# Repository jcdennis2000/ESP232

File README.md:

# ESP232

ESP8266 and ESP32 microcontrollers are great! They have built in WiFi, and Bluetooth for the ESP32, in a tiny package! However to program them they need to be put into a bootloader mode, but most programmers can’t do this for you. But now we have the ESPFlash standard!

The ESP232 uses the FTDI232 programmer, with the 1×6 0.1 inch ESPFlash convention. There is a 600mA power regulator on board, which can power the target device, and a USB B connector to connect to your computer.

For more information on the ESPFlash convention see the https://www.superhouse.tv/espflash/.

# Features:
* ESPFlash header in 1×6 0.1inch format.
* 600mA 3.3V voltage regulator.
* Power, TX and RX LEDs.
* FTDI232 USB to Serial converter.

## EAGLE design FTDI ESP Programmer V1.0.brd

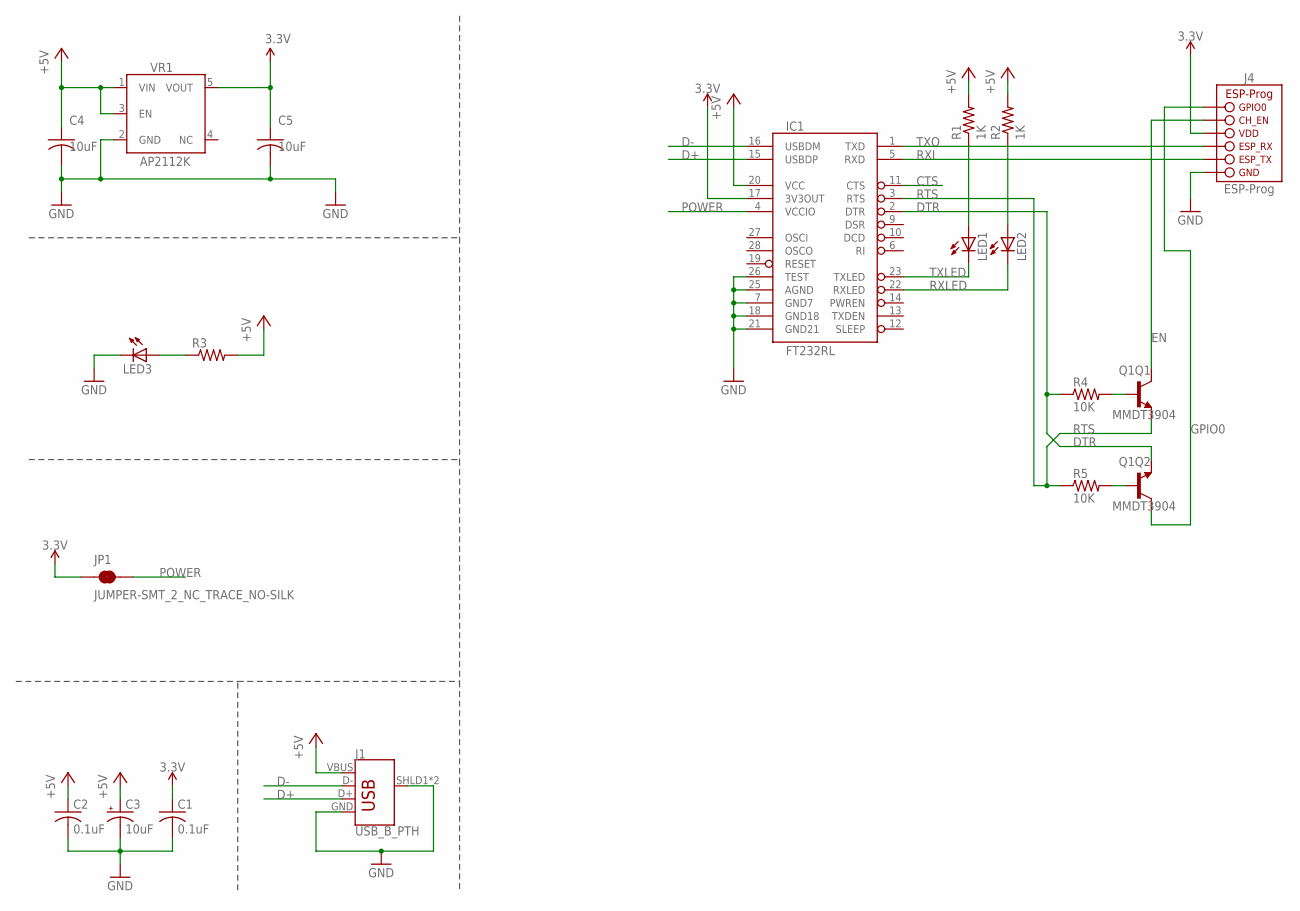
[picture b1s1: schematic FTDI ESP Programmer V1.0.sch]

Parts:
C1, C2: 0.1uF; C0603
C3: 10uF; EIA3216
C4, C5: 10uF; C0603
IC1: FT232RL; SSOP28DB
J1: USB_B_PTH; USB-B-PTH
J4: ESP-PROG-1X6-2.54-SOCKET-RA; 1X6-2.54-SOCKET-RA
JP1: JUMPER-SMT_2_NC_TRACE_NO-SILK; SMT-JUMPER_2_NC_TRACE_NO-SILK
LED1, LED2, LED3: LEDCHIP-LED0805; CHIP-LED0805
Q1: MMDT3904; SOT-363
R1, R2: 1K; R0603
R3: R-USR0603; R0603@1
R4, R5: 10K; R0603@1
VR1: AP2112KSOT25; SOT23-5

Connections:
3.3V: C1.1, C5.1, IC1.17 (3V3OUT), J4.4 (VDD), JP1.1, VR1.5 (VOUT)
+5V: C2.1, C3.+, C4.1, IC1.20 (VCC), J1.VBUS, R1.2, R2.2, R3.2, VR1.1 (VIN), VR1.3 (EN)
CTS: IC1.11 (CTS)
D+: IC1.15 (USBDP), J1.D+
D-: IC1.16 (USBDM), J1.D-
DTR: IC1.2 (DTR), Q1.1 (E), R4.1
EN: J4.5 (CH_EN), Q1.3 (C)
GND: C1.2, C2.2, C3.-, C4.2, C5.2, IC1.7 (GND7), IC1.18 (GND18), IC1.21 (GND21), IC1.25 (AGND), IC1.26 (TEST), J1.GND, J1.SHLD1 (SHIELD), J1.SHLD2 (SHIELD), J4.1 (GND), LED3.C, VR1.2 (GND)
GPIO0: J4.6 (GPIO0), Q1.6 (C)
unnamed: LED1.A, R1.1
unnamed: LED3.A, R3.1
unnamed: LED2.A, R2.1
unnamed: Q1.5 (B), R4.2
unnamed: Q1.2 (B), R5.2
POWER: IC1.4 (VCCIO), JP1.2
RTS: IC1.3 (RTS), Q1.4 (E), R5.1
RXI: IC1.5 (RXD), J4.2 (ESP_TX)
RXLED: IC1.22 (RXLED), LED2.C
TXLED: IC1.23 (TXLED), LED1.C
TXO: IC1.1 (TXD), J4.3 (ESP_RX)

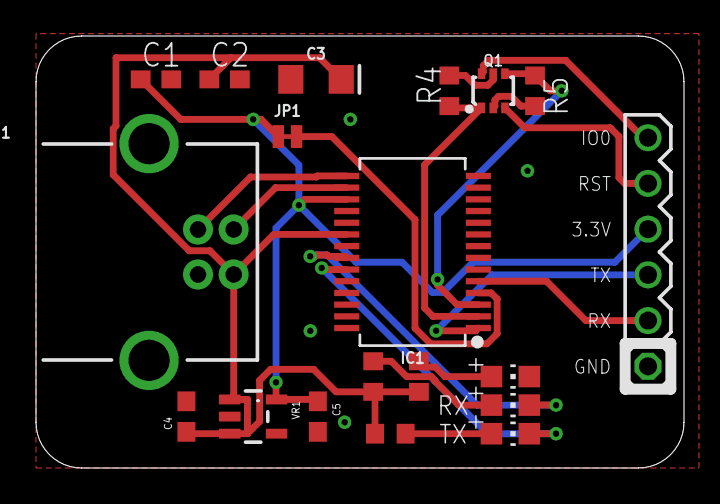
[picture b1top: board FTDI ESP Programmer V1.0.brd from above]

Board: 2 copper layers, 36.0 x 24.0 mm, 19 parts (0 on the bottom side), 19 nets.

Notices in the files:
FTDI ESP Programmer V1.0.brd:
Dennistries Ltd (c) 2020
parts and their libraries:
SparkFun-PowerSymbols: Licensing: Creative Commons ShareAlike 4.0 International - https://creativecommons.org/licenses/by-sa/4.0
